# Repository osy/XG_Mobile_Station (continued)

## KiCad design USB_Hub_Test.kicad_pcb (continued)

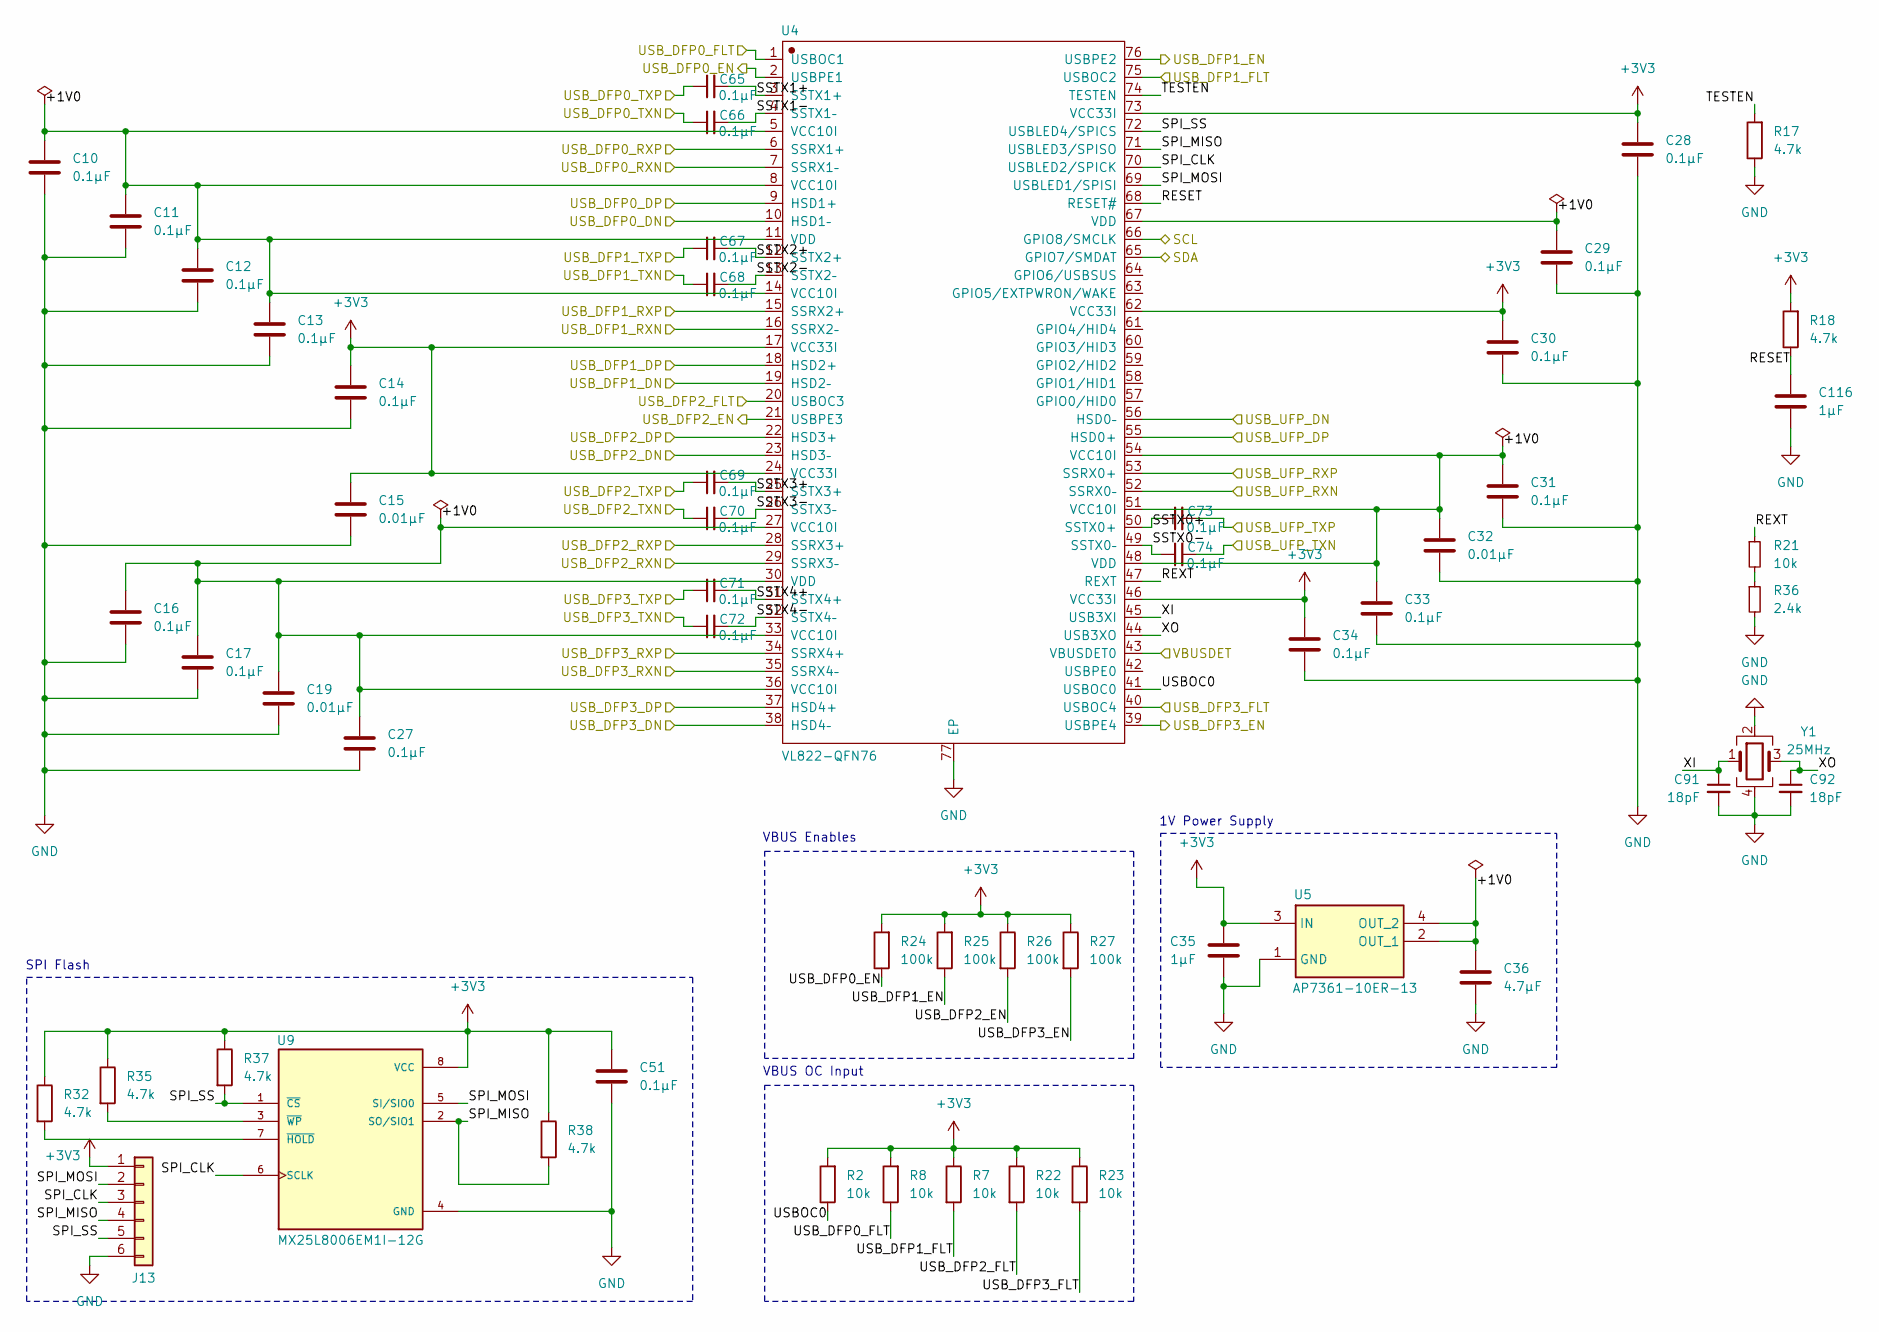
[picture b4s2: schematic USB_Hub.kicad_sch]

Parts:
C10, C11, C12, C13, C14, C16, C17, C27, C28, C29, C30, C31, C33, C34, C51, C65, C66, C67, C68, C69, C70, C71, C72, C73, C74: 0.1µF; C_0402_1005Metric; Part_Number CL05B104KB54PNC; LCSC C307331
C15, C19, C32: 0.01µF; C_0402_1005Metric; Part_Number CL05B103KB5NNNC; LCSC C15195
C35: 1µF; C_0603_1608Metric; Part_Number CL10A105KB8NNNC; LCSC C15849
C36: 4.7μF; C_0603_1608Metric; Part_Number CL10A475KO8NNNC; LCSC C19666
C91, C92: 18pF; C_0603_1608Metric; Part_Number CL10C180JB8NNNC; LCSC C1647
C116: 1µF; C_0402_1005Metric; Part_Number CL05A105KA5NQNC; LCSC C52923
J13: Conn_01x06; PinHeader_1x06_P2.54mm_Vertical; Part_Number 2.54-1*6; LCSC C5156615
R2, R7, R8, R21, R22, R23: 10k; R_0402_1005Metric; Part_Number 0402WGF1002TCE; LCSC C25744
R17, R18, R32, R35, R37, R38: 4.7k; R_0402_1005Metric; Part_Number 0402WGF4701TCE; LCSC C25900
R24, R25, R26, R27: 100k; R_0402_1005Metric; Part_Number 0402WGF1003TCE; LCSC C25741
R36: 2.4k; R_0402_1005Metric; Part_Number 0402WGF2401TCE; LCSC C25882
U4: VL822-QFN76; Part_Number VL822-QFN76; LCSC C2841047
U5: AP7361-10ER-13; SOT230P700X180-4N; Part_Number AP7361-10ER-13; LCSC C460389
U9: MX25L8006EM1I-12G; PARTREV 1.6; LCSC C106262
Y1: 25MHz; Crystal_SMD_3225-4Pin_3.2x2.5mm; Part_Number X322525MOB4SI; LCSC C9006

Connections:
+3V3: C14.1, C15.1, C28.1, C30.1, C34.1, C35.1, C51.1, J13.1, R2.2, R7.1, R8.2, R18.2, R22.1, R23.1, R24.2, R25.2, R26.1, R27.1, R32.1, R35.1, R37.1, R38.1, U4.17 (VCC33I), U4.24 (VCC33I), U4.46 (VCC33I), U4.62 (VCC33I), U4.73 (VCC33I), U5.3 (IN), U9.8 (VCC); also elsewhere on the board
/USB Hub/+1V0: C10.1, C11.1, C12.1, C13.1, C16.1, C17.1, C19.1, C27.1, C29.1, C31.1, C32.1, C33.1, C36.1, U4.5 (VCC10I), U4.8 (VCC10I), U4.11 (VDD), U4.14 (VCC10I), U4.27 (VCC10I), U4.30 (VDD), U4.33 (VCC10I), U4.36 (VCC10I), U4.48 (VDD), U4.51 (VCC10I), U4.54 (VCC10I), U4.67 (VDD), U5.2 (OUT_1), U5.4 (OUT_2)
/USB Hub/CS: J13.5, R37.2, U4.72 (USBLED4/SPICS), U9.1 (~CS); also elsewhere on the board
/USB Hub/MISO: J13.4, R38.2, U4.71 (USBLED3/SPISO), U9.2 (SO/SIO1); also elsewhere on the board
/USB Hub/MOSI: J13.2, U4.69 (USBLED1/SPISI), U9.5 (SI/SIO0); also elsewhere on the board
/USB Hub/RESET: C116.1, R18.1, U4.68 (RESET#)
/USB Hub/REXT: R21.1, U4.47 (REXT)
/USB Hub/SCL: U4.66 (GPIO8/SMCLK); also elsewhere on the board
/USB Hub/SCLK: J13.3, U4.70 (USBLED2/SPICK), U9.6 (SCLK); also elsewhere on the board
/USB Hub/SDA: U4.65 (GPIO7/SMDAT); also elsewhere on the board
/USB Hub/SSTX0+: C73.1, U4.50 (SSTX0+)
/USB Hub/SSTX0-: C74.1, U4.49 (SSTX0–)
/USB Hub/SSTX1+: C65.2, U4.3 (SSTX1+)
/USB Hub/SSTX1-: C66.2, U4.4 (SSTX1–)
/USB Hub/SSTX2+: C67.2, U4.12 (SSTX2+)
/USB Hub/SSTX2-: C68.2, U4.13 (SSTX2–)
/USB Hub/SSTX3+: C69.2, U4.25 (SSTX3+)
/USB Hub/SSTX3-: C70.2, U4.26 (SSTX3–)
/USB Hub/SSTX4+: C71.2, U4.31 (SSTX4+)
/USB Hub/SSTX4-: C72.2, U4.32 (SSTX4–)
/USB Hub/TESTEN: R17.2, U4.74 (TESTEN)
/USB Hub/USBOC0: R2.1, U4.41 (USBOC0)
/USB Hub/USB_DFP0_EN: R24.1, U4.2 (USBPE1)
/USB Hub/USB_DFP0_FLT: R8.1, U4.1 (USBOC1)
/USB Hub/USB_DFP1_EN: R25.1, U4.76 (USBPE2)
/USB Hub/USB_DFP1_FLT: R7.2, U4.75 (USBOC2)
/USB Hub/USB_DFP2_EN: R26.2, U4.21 (USBPE3)
/USB Hub/USB_DFP2_FLT: R22.2, U4.20 (USBOC3)
/USB Hub/USB_DFP3_EN: R27.2, U4.39 (USBPE4)
/USB Hub/USB_DFP3_FLT: R23.2, U4.40 (USBOC4)
/USB Hub/USB_UFP_DN: U4.56 (HSD0–); also elsewhere on the board
/USB Hub/USB_UFP_DP: U4.55 (HSD0+); also elsewhere on the board
/USB Hub/USB_UFP_RXN: U4.52 (SSRX0–); also elsewhere on the board
/USB Hub/USB_UFP_RXP: U4.53 (SSRX0+); also elsewhere on the board
/USB Hub/USB_UFP_TXN: C74.2; also elsewhere on the board
/USB Hub/USB_UFP_TXP: C73.2; also elsewhere on the board
/USB Hub/VBUSDET: U4.43 (VBUSDET0); also elsewhere on the board
/USB Hub/XI: C91.1, U4.45 (USB3XI), Y1.1
/USB Hub/XO: C92.1, U4.44 (USB3XO), Y1.3
/USB_DFP0_D1N: U4.10 (HSD1–); also elsewhere on the board
/USB_DFP0_D1P: U4.9 (HSD1+); also elsewhere on the board
/USB_DFP0_D2N: U4.19 (HSD2–); also elsewhere on the board
/USB_DFP0_D2P: U4.18 (HSD2+); also elsewhere on the board
/USB_DFP0_RX1N: U4.7 (SSRX1–); also elsewhere on the board
/USB_DFP0_RX1P: U4.6 (SSRX1+); also elsewhere on the board
/USB_DFP0_RX2N: U4.15 (SSRX2+); also elsewhere on the board
/USB_DFP0_RX2P: U4.16 (SSRX2–); also elsewhere on the board
/USB_DFP0_TX1N: C66.1; also elsewhere on the board
/USB_DFP0_TX1P: C65.1; also elsewhere on the board
/USB_DFP0_TX2N: C67.1; also elsewhere on the board
/USB_DFP0_TX2P: C68.1; also elsewhere on the board
/USB_DFP1_D1N: U4.23 (HSD3–); also elsewhere on the board
/USB_DFP1_D1P: U4.22 (HSD3+); also elsewhere on the board
/USB_DFP1_D2N: U4.38 (HSD4–); also elsewhere on the board
/USB_DFP1_D2P: U4.37 (HSD4+); also elsewhere on the board
/USB_DFP1_RX1N: U4.29 (SSRX3–); also elsewhere on the board
/USB_DFP1_RX1P: U4.28 (SSRX3+); also elsewhere on the board
/USB_DFP1_RX2N: U4.34 (SSRX4+); also elsewhere on the board
/USB_DFP1_RX2P: U4.35 (SSRX4–); also elsewhere on the board
/USB_DFP1_TX1N: C70.1; also elsewhere on the board
/USB_DFP1_TX1P: C69.1; also elsewhere on the board
/USB_DFP1_TX2N: C71.1; also elsewhere on the board
/USB_DFP1_TX2P: C72.1; also elsewhere on the board
GND: C10.2, C11.2, C12.2, C13.2, C14.2, C15.2, C16.2, C17.2, C19.2, C27.2, C28.2, C29.2, C30.2, C31.2, C32.2, C33.2, C34.2, C35.2, C36.2, C51.2, C91.2, C92.2, C116.2, J13.6, R17.1, R36.2, U4.77 (EP), U5.1 (GND), U9.4 (GND), Y1.2, Y1.4; also elsewhere on the board
unnamed: R21.2, R36.1
unnamed: R32.2, U9.7 (~HOLD)
unnamed: R35.2, U9.3 (~WP)

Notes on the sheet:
VBUS Enables
1V Power Supply
VBUS OC Input
SPI Flash

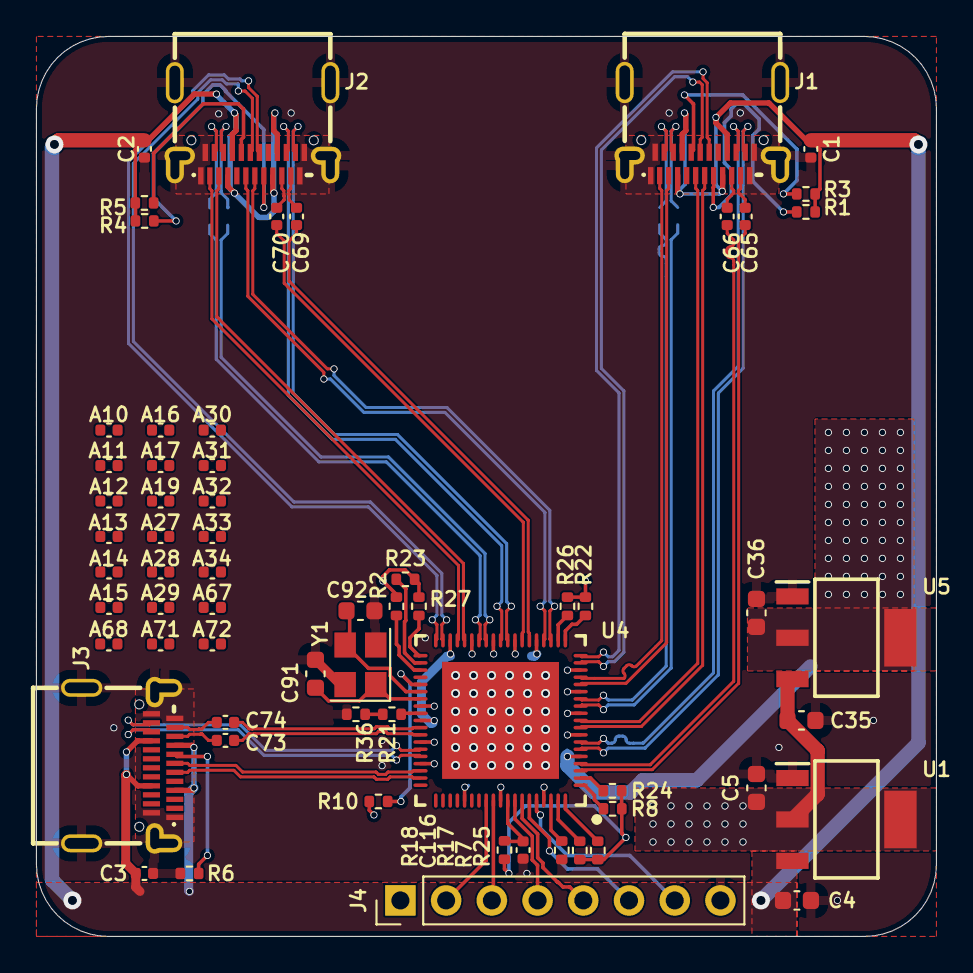
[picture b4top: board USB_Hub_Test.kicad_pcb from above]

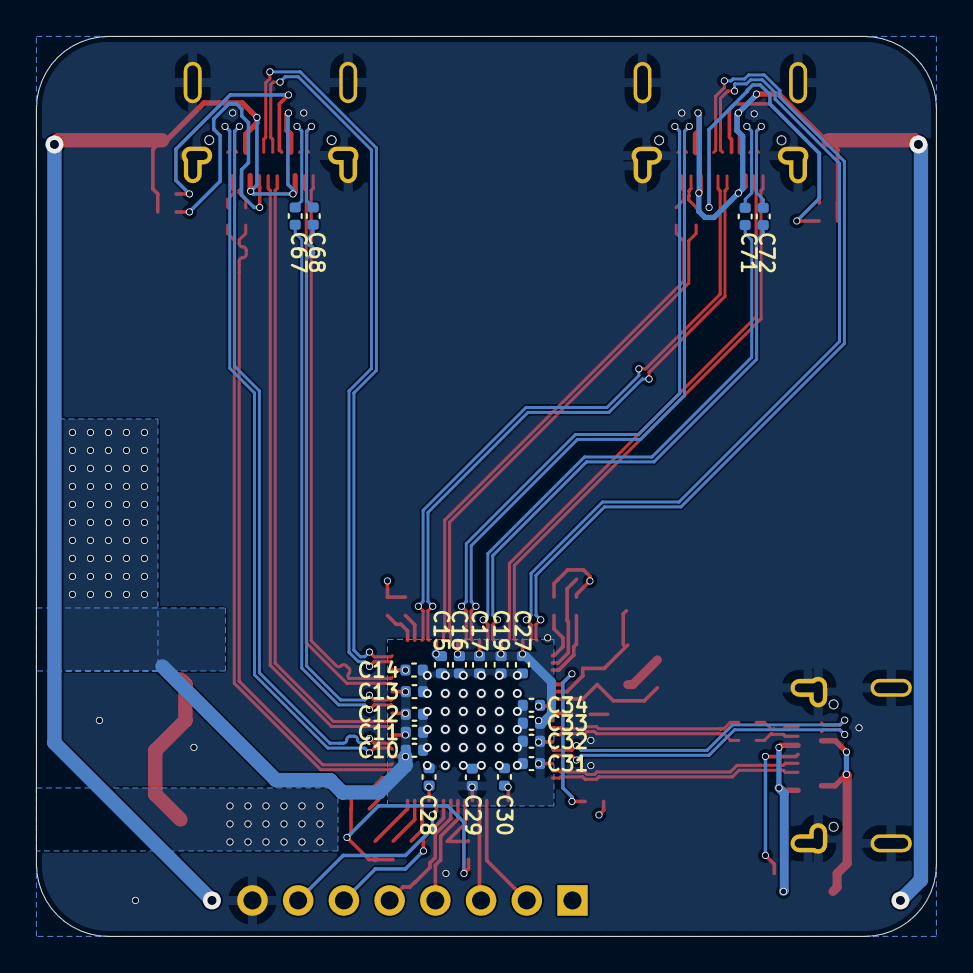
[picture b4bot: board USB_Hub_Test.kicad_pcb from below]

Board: 4 copper layers, 50.0 x 50.0 mm, 85 parts (21 on the bottom side), 71 nets.

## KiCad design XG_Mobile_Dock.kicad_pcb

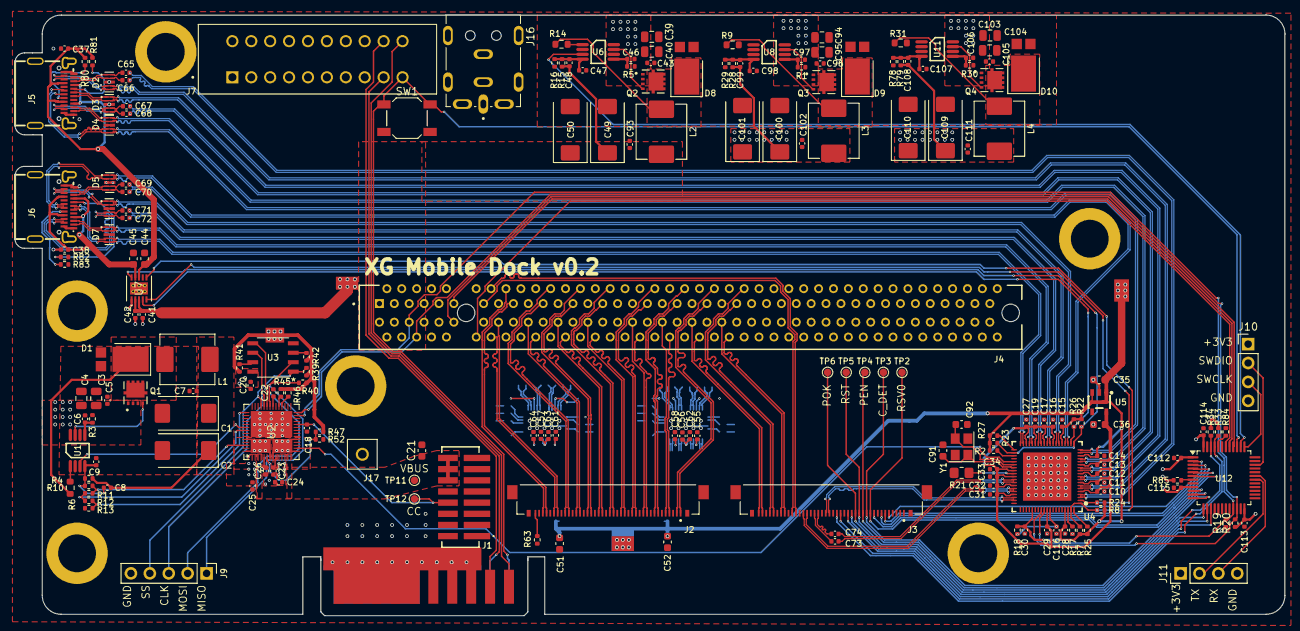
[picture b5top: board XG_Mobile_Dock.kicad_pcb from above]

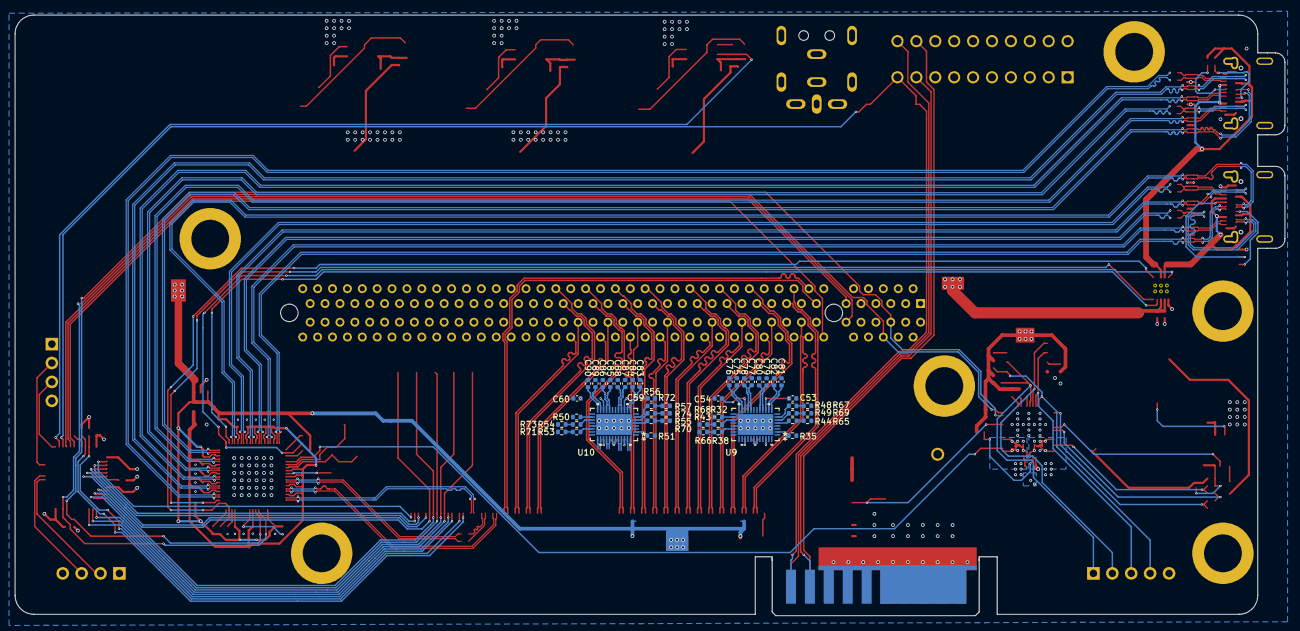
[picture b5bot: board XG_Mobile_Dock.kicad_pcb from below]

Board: 4 copper layers, 170.6 x 80.7 mm, 242 parts (46 on the bottom side), 215 nets.

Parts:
C1, C2, C49, C50, C100, C101, C109, C110: 47µF; CP_EIA-7343-43_Kemet-X
C3, C4, C39, C40, C94, C95, C103, C104: 22µF; C_0805_2012Metric
C5, C7, C10, C11, C12, C13, C14, C16, C17, C20, C27, C28, C29, C30, C31, C33, C34, C43, C65, C66, C67, C68, C69, C70, C71, C72, C73, C74, C93, C96, C102, C105, C111, C112, C113, C114: 0.1µF; C_0402_1005Metric
C6, C9, C46, C47, C97, C98, C106, C107: 1000pF; C_0402_1005Metric
C8, C48, C99, C108: 100pF; C_0402_1005Metric
C15, C19, C32: 0.01µF; C_0402_1005Metric
C18: 220pF; C_0402_1005Metric
C21, C35, C51, C52: 1µF; C_0603_1608Metric
C22, C23, C24, C25, C26, C115: 10µF; C_0402_1005Metric
C36: 4.7μF; C_0603_1608Metric
C37, C38, C41, C42, C53, C54, C55, C56, C57, C58, C59, C60, C61, C62, C63, C64: 0.1μF; C_0402_1005Metric
C44, C45: 22μF; C_0603_1608Metric
C75, C76, C77, C78, C79, C80, C81, C82, C83, C84, C85, C86, C87, C88, C89, C90: 220nF; C_0402_1005Metric
C91, C92: 22pF; C_0603_1608Metric
C116: 1µF; C_0402_1005Metric
D1, D8, D9, D10: PDS1040L-13; D_PowerDI-5
D2, D3, D4, D5, D6, D7: H5VU25U; AZ1045-04F
J1: 5-1775443-8
J2, J3: 20455-040E-76
J4: 3-2362375-4; SAMTEC_PCIE-164-02-F-D-TH-TR
J5, J6: USB_C_Receptacle; USB-C-SMD_TYPE-C-24P-QT
J7: Conn_02x10_Odd_Even; 5-5530843-0
J8: Conn_02x10_Odd_Even; 20P_Slot_Power
J9: Conn_01x05; PinHeader_1x05_P2.54mm_Vertical
J10: SWD; PinHeader_1x04_P2.54mm_Vertical
J11: UART; PinHeader_1x04_P2.54mm_Vertical
J16: 19V 5A DC; CUI_PJ-096H
J17: 8730; KEYSTONE_8730
L1, L2, L3, L4: 10µH; L_Abracon_ASPI-0630LR
Q1, Q2, Q3, Q4: AON7403; TRANS_AON7403
R1, R3, R30, R38, R43, R44, R48, R49, R53, R54, R55, R56, R57: 47k; R_0402_1005Metric
R2, R7, R8, R22, R23, R33, R34, R47, R63, R85: 10k; R_0402_1005Metric
R4: 49.9k; R_0402_1005Metric
R5: 68k; R_0402_1005Metric
R6, R9, R14, R31: 270; R_0603_1608Metric
R10, R12: 3.3k; R_0402_1005Metric
R11: 1.2k; R_0402_1005Metric
R13: 8.2k; R_0402_1005Metric
R15: 33k; R_0402_1005Metric
R16, R29: 3.9k; R_0402_1005Metric
R17, R18, R19, R20, R32, R39, R40, R41, R42, R45, R46, R50: 4.7k; R_0402_1005Metric
R21: 12.4k; R_0805_2012Metric_Pad1.20x1.40mm_HandSolder
R24, R25, R26, R27, R52: 100k; R_0402_1005Metric
R28, R65, R66, R67, R68, R69, R70, R71, R72, R73, R74, R79: 12k; R_0402_1005Metric
R35, R51, R84: 1k; R_0402_1005Metric
R78: 20k; R_0402_1005Metric
R80, R81, R82, R83: 22k; R_0402_1005Metric
SW1: SW_Push; SW_SPST_SKQG_WithStem
TP2, TP3, TP4, TP5, TP6, TP11, TP12: TestPoint_Small; TestPoint_Pad_D1.0mm
U1, U6, U8, U11: LM3489QMM/NOPB; LM3489QMM-NOPB
U2: TPS65987DDHRSHR
U3: MX25L8006EM1I-12G
U4: VL822-QFN76
U5: AP7331-10WG-7
U7: TPS2003CDRCR; DRC10_1P65X2P40_TEX
U9, U10: SN75LVPE4410RNQR
U12: STM32F030C8Tx; LQFP-48_7x7mm_P0.5mm
Y1: 25MHz; Crystal_SMD_3225-4Pin_3.2x2.5mm

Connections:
+3V3: C14.1, C15.1, C20.1, C26.1, C28.1, C30.1, C35.1, C51.1, C52.1, C55.1, C56.1, C57.1, C58.1, C61.1, C62.1, C63.1, C64.1, C108.1, C109.1, C110.1, C111.1, C112.1, C113.1, C114.1, C115.1, J3.1 (+3.3V), J3.2 (+3.3V), J3.3 (+3.3V), J3.4 (+3.3V), J4.A9, J4.A10, J4.B8, J4.B10, J10.1, J11.1, L4.2, R2.2, R7.1, R8.2, R18.2, R19.1, R20.1, R22.1, R23.1, R24.2, R25.2, R26.1, R27.1, R32.1, R33.1, R34.1, R39.1, R40.1, R41.1, R42.1, R45.2, R46.2, R47.1, R50.1, R78.1, R85.2, U2.5 (VIN_3V3), U3.8 (VCC), U4.17 (VCC33I), U4.24 (VCC33I), U4.62 (VCC33I), U4.73 (VCC33I), U5.1 (IN), U5.3 (EN), U9.31 (VDD), U9.34 (VDD), U9.35 (VDD), U9.38 (VDD), U10.31 (VDD), U10.34 (VDD), U10.35 (VDD), U10.38 (VDD), U12.1 (VDD), U12.9 (VDDA), U12.24 (VDD), U12.48 (VDD)
+5V: C41.1, C42.1, C99.1, C100.1, C101.1, C102.1, L3.2, R28.1, U7.2 (IN), U7.3 (IN)
+12V: C48.1, C49.1, C50.1, C93.1, J4.A2, J4.A3, J4.B1, J4.B2, J4.B3, L2.2, R15.1
+20V: C3.1, C4.1, C5.1, C6.1, C39.1, C40.1, C43.1, C46.1, C94.1, C95.1, C96.1, C97.1, C103.1, C104.1, C105.1, C106.1, J7.2, J7.4, J7.6, J7.8, J7.10, J7.12, J7.14, J7.16, J8.2, J8.4, J8.6, J8.8, J8.10, J8.12, J8.14, J8.16, J16.3, J16.4, Q1.1, Q2.1, Q3.1, Q4.1, R1.1, R3.1, R5.1, R30.1, U1.8 (VIN), U6.8 (VIN), U8.8 (VIN), U11.8 (VIN)
/12V_EN: U6.3 (EN), U12.38 (PA15)
/AC_LOSS: J3.15 (P_AC_LOSS), U12.14 (PA4)
/CLKN: J3.30 (PCIE_CLKN), J4.A14
/CLKP: J3.31 (PCIE_CLKP), J4.A13
/CLKREQ#: J4.B12, U12.42 (PB6)
/CON_DET: J3.11 (CON_DET), TP3.1, U12.10 (PA0)
/C_DN: J3.21 (USB_DM), U4.56 (HSD0–)
/C_DP: J3.22 (USB_DP), U4.55 (HSD0+)
/C_RXN: J3.27 (USB_TXN), U4.52 (SSRX0–)
/C_RXP: J3.28 (USB_TXP), U4.53 (SSRX0+)
/C_TXN: C74.2, J3.24 (USB_RXN)
/C_TXP: C73.2, J3.25 (USB_RXP)
/DET: J2.40 (CON_DET_TOWER#), R63.1
/LED_RED#: J3.7 (LED_R), U12.4 (PC15)
/LED_WHITE#: J3.6 (LED_W), U12.3 (PC14)
/LOCK_DET: J3.9 (CON_SW1_DET), U12.5 (PF0)
/LOCK_SW: J3.5 (LOCK_SW), U12.2 (PC13)
/MCU/RX: J11.3, U12.31 (PA10)
/MCU/SWCLK: J10.3, U12.37 (PA14)
/MCU/SWDIO: J10.2, U12.34 (PA13)
/MCU/TX: J11.2, U12.30 (PA9)
/MCU_IRQ#: J3.16 (MCU_IRQ#), U12.15 (PA5)
/PCIe Redriver/EN_SMB_0: R35.2, U9.2 (EN_SMB)
/PCIe Redriver/EN_SMB_1: R51.2, U10.2 (EN_SMB)
/PCIe Redriver/EQ0_ADDR0_0: R48.1, U9.7 (EQ0_ADDR0)
/PCIe Redriver/EQ0_ADDR0_1: R56.1, U10.7 (EQ0_ADDR0)
/PCIe Redriver/EQ1_ADDR1_0: R49.1, U9.6 (EQ1_ADDR1)
/PCIe Redriver/EQ1_ADDR1_1: R57.1, U10.6 (EQ1_ADDR1)
/PCIe Redriver/GAIN_0: R44.1, U9.5 (GAIN)
/PCIe Redriver/GAIN_1: R55.1, U10.5 (GAIN)
/PCIe Redriver/RX_DET_0: R38.1, U9.26 (RX_DET)
/PCIe Redriver/RX_DET_1: R53.1, U10.26 (RX_DET)
/PCIe Redriver/SCL: U9.3 (SCL), U10.3 (SCL)
/PCIe Redriver/SDA: U9.4 (SDA), U10.4 (SDA)
/PCIe Redriver/TX0CN: C89.2, U10.19 (TX0N)
/PCIe Redriver/TX0CP: C90.2, U10.20 (TX0P)
/PCIe Redriver/TX1CN: C85.2, U10.16 (TX1N)
/PCIe Redriver/TX1CP: C86.2, U10.17 (TX1P)
/PCIe Redriver/TX2CN: C87.2, U10.12 (TX2N)
/PCIe Redriver/TX2CP: C88.2, U10.13 (TX2P)
/PCIe Redriver/TX3CN: C83.2, U10.9 (TX3N)
/PCIe Redriver/TX3CP: C84.2, U10.10 (TX3P)
/PCIe Redriver/TX4CN: C75.2, U9.19 (TX0N)
/PCIe Redriver/TX4CP: C76.2, U9.20 (TX0P)
/PCIe Redriver/TX5CN: C77.2, U9.16 (TX1N)
/PCIe Redriver/TX5CP: C78.2, U9.17 (TX1P)
/PCIe Redriver/TX6CN: C79.2, U9.12 (TX2N)
/PCIe Redriver/TX6CP: C80.2, U9.13 (TX2P)
/PCIe Redriver/TX7CN: C81.2, U9.9 (TX3N)
/PCIe Redriver/TX7CP: C82.2, U9.10 (TX3P)
/PCIe Redriver/VOD_0: R43.1, U9.23 (VOD)
/PCIe Redriver/VOD_1: R54.1, U10.23 (VOD)
/PERST#: J4.A11, U12.41 (PB5)
/PWREN#: J3.12 (PWR_EN#), TP4.1, U12.11 (PA1)
/PWROK: J3.14 (PWROK), TP6.1, U12.13 (PA3)
/PWR_SW: J7.19, J8.19, SW1.1, U12.39 (PB3)
/RST#: J3.13 (RST#), TP5.1, U12.12 (PA2)
/RSV0: J3.10, TP2.1, U12.6 (PF1)
/RX0N: J2.37 (PCIE_TXN0), J4.A17
/RX0P: J2.38 (PCIE_TXP0), J4.A16
/RX1N: J2.31 (PCIE_TXN1), J4.A21
/RX1P: J2.32 (PCIE_TXP1), J4.A22
/RX2N: J2.25 (PCIE_TXN2), J4.A25
/RX2P: J2.26 (PCIE_TXP2), J4.A26
/RX3N: J2.19 (PCIE_TXN3), J4.A29
/RX3P: J2.20 (PCIE_TXP3), J4.A30
/RX4N: J2.13 (PCIE_TXN4), J4.A35
/RX4P: J2.14 (PCIE_TXP4), J4.A36
/RX5N: J2.7 (PCIE_TXN5), J4.A39
/RX5P: J2.8 (PCIE_TXP5), J4.A40
/RX6N: J2.1 (PCIE_TXN6), J4.A43
/RX6P: J2.2 (PCIE_TXP6), J4.A44
/RX7N: J3.36 (PCIE_TXN7), J4.A47
/RX7P: J3.37 (PCIE_TXP7), J4.A48
/SCL1: J3.19 (SMB1_CLK), R33.2, U12.45 (PB8)
/SCL2: J4.B5, R19.2, U2.27 (I2C1_SCL), U4.66 (GPIO8/SMCLK), U12.21 (PB10)
/SDA1: J3.18 (SMB1_DAT), R34.2, U12.46 (PB9)
/SDA2: J4.B6, R20.2, U2.28 (I2C1_SDA), U4.65 (GPIO7/SMDAT), U12.22 (PB11)
/TX0N: J2.34 (PCIE_RXN0), J4.B15
/TX0P: J2.35 (PCIE_RXP0), J4.B14
/TX1N: J2.28 (PCIE_RXN1), J4.B20
/TX1P: J2.29 (PCIE_RXP1), J4.B19
/TX2N: J2.22 (PCIE_RXN2), J4.B24
/TX2P: J2.23 (PCIE_RXP2), J4.B23
/TX3N: J2.16 (PCIE_RXN3), J4.B28
/TX3P: J2.17 (PCIE_RXP3), J4.B27
/TX4N: J2.10 (PCIE_RXN4), J4.B34
/TX4P: J2.11 (PCIE_RXP4), J4.B33
/TX5N: J2.4 (PCIE_RXN5), J4.B38
/TX5P: J2.5 (PCIE_RXP5), J4.B37
/TX6N: J3.39 (PCIE_RXN6), J4.B42
/TX6P: J3.40 (PCIE_RXP6), J4.B41
/TX7N: J3.33 (PCIE_RXN7), J4.B46
/TX7P: J3.34 (PCIE_RXP7), J4.B45
/USB C DFPs/USB_DFP0_D1N: D3.2 (I/O_2), D3.9 (NC), J5.A7 (D-), U4.10 (HSD1–)
/USB C DFPs/USB_DFP0_D1P: D3.1 (I/O_1), D3.10 (NC), J5.A6 (D+), U4.9 (HSD1+)
/USB C DFPs/USB_DFP0_D2N: D4.5 (I/O_4), D4.6 (NC), J5.B7 (D-), U4.19 (HSD2–)
/USB C DFPs/USB_DFP0_D2P: D4.4 (I/O_3), D4.7 (NC), J5.B6 (D+), U4.18 (HSD2+)
/USB C DFPs/USB_DFP0_RX1N: D2.5 (I/O_4), D2.6 (NC), J5.B10 (RX1-), U4.7 (SSRX1–)
/USB C DFPs/USB_DFP0_RX1P: D2.4 (I/O_3), D2.7 (NC), J5.B11 (RX1+), U4.6 (SSRX1+)
/USB C DFPs/USB_DFP0_RX2N: D4.1 (I/O_1), D4.10 (NC), J5.A10 (RX2-), U4.15 (SSRX2+)
/USB C DFPs/USB_DFP0_RX2P: D4.2 (I/O_2), D4.9 (NC), J5.A11 (RX2+), U4.16 (SSRX2–)
/USB C DFPs/USB_DFP0_TX1N: C66.1, D2.2 (I/O_2), D2.9 (NC), J5.A3 (TX1-)
/USB C DFPs/USB_DFP0_TX1P: C65.1, D2.1 (I/O_1), D2.10 (NC), J5.A2 (TX1+)
/USB C DFPs/USB_DFP0_TX2N: C67.1, D3.4 (I/O_3), D3.7 (NC), J5.B3 (TX2-)
/USB C DFPs/USB_DFP0_TX2P: C68.1, D3.5 (I/O_4), D3.6 (NC), J5.B2 (TX2+)
/USB C DFPs/USB_DFP0_VBUS: C37.1, C44.1, J5.A4 (VBUS), J5.A9 (VBUS), J5.B4 (VBUS), J5.B9 (VBUS), R80.2, R81.1, U7.8 (OUT2)
/USB C DFPs/USB_DFP1_D1N: D7.5 (I/O_4), D7.6 (NC), J6.A7 (D-), U4.38 (HSD4–)
/USB C DFPs/USB_DFP1_D1P: D7.4 (I/O_3), D7.7 (NC), J6.A6 (D+), U4.37 (HSD4+)
/USB C DFPs/USB_DFP1_D2N: D5.2 (I/O_2), D5.9 (NC), J6.B7 (D-), U4.23 (HSD3–)
/USB C DFPs/USB_DFP1_D2P: D5.1 (I/O_1), D5.10 (NC), J6.B6 (D+), U4.22 (HSD3+)
/USB C DFPs/USB_DFP1_RX1N: D6.2 (I/O_2), D6.9 (NC), J6.B10 (RX1-), U4.29 (SSRX3–)
/USB C DFPs/USB_DFP1_RX1P: D6.1 (I/O_1), D6.10 (NC), J6.B11 (RX1+), U4.28 (SSRX3+)
/USB C DFPs/USB_DFP1_RX2N: D7.1 (I/O_1), D7.10 (NC), J6.A10 (RX2-), U4.34 (SSRX4+)
/USB C DFPs/USB_DFP1_RX2P: D7.2 (I/O_2), D7.9 (NC), J6.A11 (RX2+), U4.35 (SSRX4–)
/USB C DFPs/USB_DFP1_TX1N: C70.1, D5.5 (I/O_4), D5.6 (NC), J6.A3 (TX1-)
/USB C DFPs/USB_DFP1_TX1P: C69.1, D5.4 (I/O_3), D5.7 (NC), J6.A2 (TX1+)
/USB C DFPs/USB_DFP1_TX2N: C71.1, D6.4 (I/O_3), D6.7 (NC), J6.B3 (TX2-)
/USB C DFPs/USB_DFP1_TX2P: C72.1, D6.5 (I/O_4), D6.6 (NC), J6.B2 (TX2+)
/USB C DFPs/USB_DFP1_VBUS: C38.1, C45.1, J6.A4 (VBUS), J6.A9 (VBUS), J6.B4 (VBUS), J6.B9 (VBUS), R82.2, R83.1, U7.9 (OUT1)
/USB Hub/+1V0: C10.1, C11.1, C12.1, C13.1, C16.1, C17.1, C19.1, C27.1, C29.1, C31.1, C32.1, C33.1, C34.1, C36.1, U4.5 (VCC10I), U4.8 (VCC10I), U4.11 (VDD), U4.14 (VCC10I), U4.27 (VCC10I), U4.30 (VDD), U4.33 (VCC10I), U4.36 (VCC10I), U4.46 (VCC33I), U4.48 (VDD), U4.51 (VCC10I), U4.54 (VCC10I), U4.67 (VDD), U5.5 (OUT)
/USB Hub/RESET: C116.1, R18.1, U4.68 (RESET#)
/USB Hub/REXT: R21.1, U4.47 (REXT)
/USB Hub/SSTX0+: C73.1, U4.50 (SSTX0+)
/USB Hub/SSTX0-: C74.1, U4.49 (SSTX0–)
/USB Hub/SSTX1+: C65.2, U4.3 (SSTX1+)
/USB Hub/SSTX1-: C66.2, U4.4 (SSTX1–)
/USB Hub/SSTX2+: C67.2, U4.12 (SSTX2+)
/USB Hub/SSTX2-: C68.2, U4.13 (SSTX2–)
/USB Hub/SSTX3+: C69.2, U4.25 (SSTX3+)
/USB Hub/SSTX3-: C70.2, U4.26 (SSTX3–)
/USB Hub/SSTX4+: C71.2, U4.31 (SSTX4+)
/USB Hub/SSTX4-: C72.2, U4.32 (SSTX4–)
/USB Hub/TESTEN: R17.2, U4.74 (TESTEN)
/USB Hub/USBOC0: R2.1, U4.41 (USBOC0)
/USB Hub/USB_DFP0_EN: R24.1, U4.2 (USBPE1), U7.5 (EN2)
/USB Hub/USB_DFP0_FLT: R7.2, R8.1, U4.1 (USBOC1), U4.75 (USBOC2), U7.6 (*FLT2)
/USB Hub/USB_DFP1_EN: R25.1, U4.76 (USBPE2)
/USB Hub/USB_DFP2_EN: R26.2, U4.21 (USBPE3), U7.4 (EN1)
/USB Hub/USB_DFP2_FLT: R22.2, R23.2, U4.20 (USBOC3), U4.40 (USBOC4), U7.10 (*FLT1)
/USB Hub/USB_DFP3_EN: R27.2, U4.39 (USBPE4)
/USB Hub/VBUSDET: U2.16 (GPIO0), U4.43 (VBUSDET0)
/USB Hub/XI: C91.1, U4.45 (USB3XI), Y1.1
/USB Hub/XO: C92.1, U4.44 (USB3XO), Y1.3
/USB PD Charger/BOOT: R47.2, R52.1, U2.6 (ADCIN1)
/USB PD Charger/CC: C18.1, J1.13 (CC), TP12.1, U2.24 (C_CC1)
/USB PD Charger/DRAIN1: U2.8 (DRAIN1), U2.15 (DRAIN1), U2.19 (DRAIN1), U2.58 (DRAIN1)
/USB PD Charger/DRAIN2: U2.7 (DRAIN2), U2.52 (DRAIN2), U2.56 (DRAIN2), U2.57 (DRAIN2)
/USB PD Charger/LDO_3V3: C23.1, U2.9 (LDO_3V3)
/USB PD Charger/PDO_1: R12.2, R13.1, U2.43 (GPIO15)
/USB PD Charger/PDO_2: R11.2, R12.1, U2.49 (GPIO17)
/USB PD Charger/PDO_3: R10.2, R11.1, U2.54 (GPIO20)
/USB PD Charger/POWER_EN: U1.3 (EN), U2.48 (GPIO16)
/USB PD Charger/SPI_CLK: J9.3, U2.38 (SPI_CLK), U3.6 (SCLK)
/USB PD Charger/SPI_MISO: J9.1, R40.2, U2.36 (SPI_MISO), U3.2 (SO/SIO1)
/USB PD Charger/SPI_MOSI: J9.2, U2.37 (SPI_MOSI), U3.5 (SI/SIO0)
/USB PD Charger/SPI_SS: J9.4, R39.2, U2.39 (SPI_SS), U3.1 (~CS)
/USB PD Charger/VBUS: C21.1, J1.9 (VBUS), J1.10 (VBUS), J1.11 (VBUS), TP11.1, U2.3 (VBUS2), U2.4 (VBUS2), U2.13 (VBUS1), U2.14 (VBUS1)
/WAKE#: J4.B11, U12.40 (PB4)
GND: C1.2, C2.2, C3.2, C4.2, C5.2, C7.2, C9.2, C10.2, C11.2, C12.2, C13.2, C14.2, C15.2, C16.2, C17.2, C18.2, C19.2, C20.2, C21.2, C22.2, C23.2, C24.2, C25.2, C26.2, C27.2, C28.2, C29.2, C30.2, C31.2, C32.2, C33.2, C34.2, C35.2, C36.2, C37.2, C38.2, C39.2, C40.2, C41.2, C42.2, C43.2, C44.2, C45.2, C47.2, C49.2, C50.2, C51.2, C52.2, C53.2, C54.2, C55.2, C56.2, C57.2, C58.2, C59.2, C60.2, C61.2, C62.2, C63.2, C64.2, C91.2, C92.2, C93.2, C94.2, C95.2, C96.2, C98.2, C100.2, C101.2, C102.2, C103.2, C104.2, C105.2, C107.2, C109.2, C110.2, C111.2, C112.2, C113.2, C114.2, C115.2, C116.2, D1.2 (A), D2.3 (GND), D2.8 (GND), D3.3 (GND), D3.8 (GND), D4.3 (GND), D4.8 (GND), D5.3 (GND), D5.8 (GND), D6.3 (GND), D6.8 (GND), D7.3 (GND), D7.8 (GND), D8.2 (A), D9.2 (A), D10.2 (A), J1.14 (GND), J1.15 (GND), J1.16 (GND), J2.3 (GND), J2.6 (GND), J2.9 (GND), J2.12 (GND), J2.15 (GND), J2.18 (GND), J2.21 (GND), J2.24 (GND), J2.27 (GND), J2.30 (GND), J2.33 (GND), J2.36 (GND), J2.39 (GND), J2.S1 (SHIELD), J2.S2 (SHIELD), J2.S3 (SHIELD), J2.S4 (SHIELD), J3.17 (GND), J3.20 (GND), J3.23 (GND), J3.26 (GND), J3.29 (GND), J3.32 (GND), J3.35 (GND), J3.38 (GND), J3.S1 (SHIELD), J3.S2 (SHIELD), J3.S3 (SHIELD), J3.S4 (SHIELD), J4.A4, J4.A12, J4.A15, J4.A18, J4.A20, J4.A23, J4.A24, J4.A27, J4.A28, J4.A31, J4.A34, J4.A37, J4.A38, J4.A41, J4.A42, J4.A45, J4.A46, J4.A49, J4.A51, J4.A54, J4.A55, J4.A58, J4.A59, J4.A62, J4.A63, J4.A66, J4.A67, J4.A70, J4.A71, J4.A74, J4.A75, J4.A78, J4.A79, J4.A82, J4.B4, J4.B7, J4.B13, J4.B16, J4.B18, J4.B21, J4.B22, J4.B25, J4.B26, J4.B29, J4.B32, J4.B35, J4.B36, J4.B39, J4.B40, J4.B43, J4.B44, J4.B47, J4.B49, J4.B52, J4.B53, J4.B56, J4.B57, J4.B60, J4.B61, J4.B64, J4.B65, J4.B68, J4.B69, J4.B72, J4.B73, J4.B76, J4.B77, J4.B80, J5.A1 (GND), J5.A12 (GND), J5.B1 (GND), J5.B12 (GND), J5.S1 (SHIELD), J6.A1 (GND), J6.A12 (GND), J6.B1 (GND)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
unnamed: C53.1, U9.11 (VREG)
unnamed: C54.1, U9.18 (VREG)
unnamed: C59.1, U10.11 (VREG)
unnamed: C60.1, U10.18 (VREG)
unnamed: D1.1 (K), L1.1, Q1.5_8, R6.2
unnamed: D8.1 (K), L2.1, Q2.5_8, R14.2
unnamed: D9.1 (K), L3.1, Q3.5_8, R9.2
unnamed: D10.1 (K), L4.1, Q4.5_8, R31.2
unnamed: J5.A5 (CC1), R80.1
unnamed: J5.B5 (CC2), R81.2
unnamed: J6.A5 (CC1), R82.1
unnamed: J6.B5 (CC2), R83.2
unnamed: J7.17, J8.17
unnamed: J7.18, J8.18
unnamed: J7.20, J8.20
unnamed: R38.2, R66.1
unnamed: R43.2, R68.1
unnamed: R44.2, R65.1
unnamed: R48.2, R67.1
unnamed: R49.2, R69.1
unnamed: R53.2, R71.1
unnamed: R54.2, R73.1
unnamed: R55.2, R70.1
unnamed: R56.2, R72.1
unnamed: R57.2, R74.1
unnamed: C6.2, R3.2, U1.5 (ADJ)
unnamed: C8.2, C9.1, R4.2, R10.1, U1.4 (FB)
unnamed: R6.1, U1.1 (ISENSE)
unnamed: Q1.4, U1.7 (PGATE)
unnamed: R46.1, U2.32 (I2C2_SCL)
unnamed: R45.1, U2.33 (I2C2_SDA)
unnamed: C22.1, U2.35 (LDO_1V8)
unnamed: R41.2, U3.7 (~HOLD)
unnamed: R42.2, U3.3 (~WP)
unnamed: C46.2, R5.2, U6.5 (ADJ)
unnamed: C47.1, C48.2, R15.2, R16.2, U6.4 (FB)
unnamed: R14.1, U6.1 (ISENSE)
unnamed: Q2.4, U6.7 (PGATE)
unnamed: C97.2, R1.2, U8.5 (ADJ)
unnamed: C98.1, C99.2, R28.2, R29.2, U8.4 (FB)
unnamed: R9.1, U8.1 (ISENSE)
unnamed: Q3.4, U8.7 (PGATE)
unnamed: R32.2, U9.22 (RSVD2)
unnamed: R50.2, U10.22 (RSVD2)
unnamed: C106.2, R30.2, U11.5 (ADJ)
unnamed: C107.1, C108.2, R78.2, R79.1, U11.4 (FB)
unnamed: R31.1, U11.1 (ISENSE)
unnamed: Q4.4, U11.7 (PGATE)
unnamed: R84.2, U12.44 (BOOT0)
unnamed: R85.1, U12.7 (NRST)
PP_HV: C1.1, C2.1, C7.1, C8.1, C24.1, C25.1, L1.2, R4.1, U2.1 (PP_HV2), U2.2 (PP_HV2), U2.11 (PP_HV1), U2.12 (PP_HV1)

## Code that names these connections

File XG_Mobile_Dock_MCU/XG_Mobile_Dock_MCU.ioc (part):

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Mcu.Name=STM32F030C8Tx
Mcu.Package=LQFP48
Mcu.UserName=STM32F030C8Tx
PA0.GPIOParameters=GPIO_PuPd,GPIO_Label,GPIO_ModeDefaultEXTI
PA0.GPIO_Label=CON_DET
PA0.GPIO_ModeDefaultEXTI=GPIO_MODE_IT_RISING_FALLING
PA0.GPIO_PuPd=GPIO_PULLUP
PA0.Signal=GPXTI0
PA1.GPIOParameters=GPIO_PuPd,GPIO_Label,GPIO_ModeDefaultEXTI
PA1.GPIO_Label=PWREN
PA1.GPIO_ModeDefaultEXTI=GPIO_MODE_IT_RISING_FALLING
PA1.GPIO_PuPd=GPIO_PULLUP
PA1.Signal=GPXTI1
PA10.Mode=Asynchronous
PA10.Signal=USART1_RX
PA12.GPIOParameters=PinState,GPIO_Label
PA12.GPIO_Label=FAN_ON
PA12.PinState=GPIO_PIN_RESET
PA12.Signal=GPIO_Output
PA13.Mode=Serial_Wire
PA13.Signal=SYS_SWDIO
PA14.Mode=Serial_Wire
PA14.Signal=SYS_SWCLK
PA15.GPIOParameters=PinState,GPIO_PuPd,GPIO_Label,GPIO_ModeDefaultOutputPP
PA15.GPIO_Label=PCI_12V_EN
PA15.GPIO_ModeDefaultOutputPP=GPIO_MODE_OUTPUT_OD
PA15.GPIO_PuPd=GPIO_NOPULL
PA15.PinState=GPIO_PIN_RESET
PA15.Signal=GPIO_Output
PA2.GPIOParameters=GPIO_PuPd,GPIO_Label,GPIO_ModeDefaultEXTI
PA2.GPIO_Label=RST
PA2.GPIO_ModeDefaultEXTI=GPIO_MODE_IT_RISING_FALLING
PA2.GPIO_PuPd=GPIO_PULLUP
PA2.Signal=GPXTI2
PA3.GPIOParameters=PinState,GPIO_PuPd,GPIO_Label,GPIO_ModeDefaultOutputPP
PA3.GPIO_Label=PWROK
PA3.GPIO_ModeDefaultOutputPP=GPIO_MODE_OUTPUT_PP
PA3.GPIO_PuPd=GPIO_NOPULL
PA3.PinState=GPIO_PIN_RESET
PA3.Signal=GPIO_Output
PA4.GPIOParameters=PinState,GPIO_PuPd,GPIO_Label,GPIO_ModeDefaultOutputPP
PA4.GPIO_Label=AC_LOSS
PA4.GPIO_ModeDefaultOutputPP=GPIO_MODE_OUTPUT_PP
PA4.GPIO_PuPd=GPIO_PULLDOWN
PA4.PinState=GPIO_PIN_RESET
PA4.Signal=GPIO_Output
PA5.GPIOParameters=PinState,GPIO_PuPd,GPIO_Label,GPIO_ModeDefaultOutputPP
PA5.GPIO_Label=MCU_IRQ
PA5.GPIO_ModeDefaultOutputPP=GPIO_MODE_OUTPUT_OD
PA5.GPIO_PuPd=GPIO_PULLUP
PA5.PinState=GPIO_PIN_SET
PA5.Signal=GPIO_Output
PA9.Mode=Asynchronous
PA9.Signal=USART1_TX
PB1.Mode=IN9
PB1.Signal=ADC_IN9
PB10.Mode=I2C
PB10.Signal=I2C2_SCL
PB11.Mode=I2C
PB11.Signal=I2C2_SDA
PB12.GPIOParameters=PinState,GPIO_PuPd,GPIO_Label,GPIO_ModeDefaultOutputPP
PB12.GPIO_Label=PWR_SW
PB12.GPIO_ModeDefaultOutputPP=GPIO_MODE_OUTPUT_OD
PB12.GPIO_PuPd=GPIO_NOPULL
PB12.PinState=GPIO_PIN_SET
PB12.Signal=GPIO_Output
PB13.GPIOParameters=GPIO_PuPd,GPIO_Label
PB13.GPIO_Label=SYS_ON
PB13.GPIO_PuPd=GPIO_PULLDOWN
PB13.Signal=GPIO_Input
PB14.GPIOParameters=GPIO_PuPd,GPIO_Label
PB14.GPIO_Label=SYS_DET
PB14.GPIO_PuPd=GPIO_PULLUP
PB14.Signal=GPIO_Input
PB2.GPIOParameters=PinState,GPIO_Label
PB2.GPIO_Label=HP_SHDN
PB2.PinState=GPIO_PIN_SET
PB2.Signal=GPIO_Output
PB3.GPIOParameters=GPIO_Speed,PinState,GPIO_Label
PB3.GPIO_Label=FAN_PWM
PB3.GPIO_Speed=GPIO_SPEED_FREQ_HIGH
PB3.PinState=GPIO_PIN_RESET
PB3.Signal=GPIO_Output
PB4.GPIOParameters=PinState,GPIO_PuPd,GPIO_Label,GPIO_ModeDefaultOutputPP
PB4.GPIO_Label=WAKE
PB4.GPIO_ModeDefaultOutputPP=GPIO_MODE_OUTPUT_OD
PB4.GPIO_PuPd=GPIO_PULLUP
PB4.PinState=GPIO_PIN_SET
PB4.Signal=GPIO_Output
PB5.GPIOParameters=PinState,GPIO_PuPd,GPIO_Label,GPIO_ModeDefaultOutputPP
PB5.GPIO_Label=PERST
PB5.GPIO_ModeDefaultOutputPP=GPIO_MODE_OUTPUT_OD
PB5.GPIO_PuPd=GPIO_PULLUP
PB5.PinState=GPIO_PIN_SET
PB5.Signal=GPIO_Output
PB6.GPIOParameters=PinState,GPIO_PuPd,GPIO_Label,GPIO_ModeDefaultOutputPP
PB6.GPIO_Label=CLKREQ
PB6.GPIO_ModeDefaultOutputPP=GPIO_MODE_OUTPUT_OD
PB6.GPIO_PuPd=GPIO_PULLUP
PB6.PinState=GPIO_PIN_SET
PB6.Signal=GPIO_Output
PB8.Mode=I2C
PB8.Signal=I2C1_SCL
PB9.Mode=I2C
PB9.Signal=I2C1_SDA
PC13.GPIOParameters=GPIO_PuPd,GPIO_Label,GPIO_ModeDefaultEXTI
PC13.GPIO_Label=LOCK_SW
PC13.GPIO_ModeDefaultEXTI=GPIO_MODE_IT_RISING_FALLING
PC13.GPIO_PuPd=GPIO_PULLUP
PC13.Signal=GPXTI13
PC14-OSC32_IN.GPIOParameters=PinState,GPIO_PuPd,GPIO_Label,GPIO_ModeDefaultOutputPP
PC14-OSC32_IN.GPIO_Label=LED_WHITE
PC14-OSC32_IN.GPIO_ModeDefaultOutputPP=GPIO_MODE_OUTPUT_OD
PC14-OSC32_IN.GPIO_PuPd=GPIO_NOPULL
PC14-OSC32_IN.PinState=GPIO_PIN_SET
PC14-OSC32_IN.Signal=GPIO_Output
PC15-OSC32_OUT.GPIOParameters=PinState,GPIO_PuPd,GPIO_Label,GPIO_ModeDefaultOutputPP
PC15-OSC32_OUT.GPIO_Label=LED_RED
PC15-OSC32_OUT.GPIO_ModeDefaultOutputPP=GPIO_MODE_OUTPUT_OD
PC15-OSC32_OUT.GPIO_PuPd=GPIO_NOPULL
PC15-OSC32_OUT.PinState=GPIO_PIN_SET
PC15-OSC32_OUT.Signal=GPIO_Output
PF0-OSC_IN.GPIOParameters=GPIO_Label
PF0-OSC_IN.GPIO_Label=LOCK_DET
PF0-OSC_IN.Signal=GPIO_Output
PF1-OSC_OUT.GPIOParameters=GPIO_Label
PF1-OSC_OUT.GPIO_Label=RSV0
PF1-OSC_OUT.Signal=GPIO_Input
PF7.GPIOParameters=PinState,GPIO_PuPd,GPIO_Label,GPIO_ModeDefaultOutputPP
PF7.GPIO_Label=CASE_LED
PF7.GPIO_ModeDefaultOutputPP=GPIO_MODE_OUTPUT_OD
PF7.GPIO_PuPd=GPIO_NOPULL
PF7.PinState=GPIO_PIN_SET
PF7.Signal=GPIO_Output
RCC.SYSCLKFreq_VALUE=32000000
RCC.SYSCLKSource=RCC_SYSCLKSOURCE_PLLCLK
board=custom

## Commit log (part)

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2024-03-23 Updated schematics
2024-03-23 Continue working on board layout
2024-03-24 Lay out more components
2024-03-24 Updated board layout
2024-03-25 Fix unconnected GND
2024-03-25 Misplaced one track on 20P connector
2024-04-21 Fixed ATX-24 pinout numbering
2024-04-21 Add power components
2024-04-21 Replace TI USB PD with ST USB PD
2024-04-24 Add TPS65987D charger circuit
2024-04-24 Replace AOSP21321 with AON7403 and update 3D models
2024-04-25 new power blocks
2024-04-25 Laid out components for power circuits
2024-04-26 Rewired PCIe without redriver
2024-04-26 Add CC values to DFP ports
2024-04-26 Renamed some connector pins
2024-04-27 Added MCU
2024-04-27 Fixed all DRC errors
2024-04-27 Replaced 12.4k resistor with two basic parts
2024-04-28 Increased inductor size
2024-05-01 Add initial MCU project
2024-05-04 Fixed USB Hub wrong net 1V0 -> 3V3
2024-05-05 Added initial FSM in MCU code
2024-05-11 Improvements to board
    * Break up power switch into input and output signals
    * Removed POWER_EN from USB PD charger (GPIO does not work due to one event per pin)
    * Added MOSFET to buffer GPIO output from PD IC
2024-05-15 Implemented MCU firmware
2024-05-18 Fixed power connector, PCIe direction, and MCU changes
2024-05-18 Add MCU schematics
2024-05-18 Update board version
2024-05-18 Added documentation
2024-05-18 Remove PCIe leech project
2024-07-01 Update firmware for rev 3 board
2024-07-03 Fix flipped MOSFETs for PDO signals
2024-07-03 Mislabeled I2C pin GND and 3V3
2024-07-05 Fix external board power toggle
2024-07-14 Replace TH PCI-E slot with SMD
2024-07-14 Add external board detect pin to MCU
2024-07-14 Fix missing GND connection & update name
2024-07-18 Implemented I2C communication
2024-07-18 Add external board detect to MCU
2024-07-18 Add debug config
2024-07-19 Added 3D model of new PCI-E slot
2024-07-21 Add XGMActivator project
2024-07-21 Fix I2C issue when 0xE6 is spammed
2024-07-21 Updated documentation
2024-07-21 Make sure photo credits show up
2024-07-21 Updated links to references
2024-07-21 Misnamed gitignore
2024-07-21 Updated diary
2024-07-21 Confirmed that only PCIe 3.0 works
2024-07-28 Increase thermal mass under 1V0 LDO
2024-07-28 Ensure SPI flash is powered on even when board loses power
2024-07-28 Move 1V0 LDO farther away from USB IC to reduce thermal load
2024-07-28 Bumped version to v0.4.1
2024-07-31 Replace AP7331-10WG-7 with AP7361-10ER-13 to handle power draw
2024-08-02 Increased heat sink area of 1V0 LDO
2024-08-04 Add TI PD project
2024-08-04 XGMActivator: fix typo
2024-08-06 Add power riser design
2024-08-06 MCU: move external board toggle to cable connect time
2024-08-06 docs: update diary with completed build
2024-08-07 pcb: added lite variant
2024-08-07 docs: updated build guide for lite builds
2024-08-08 pcb: redesign lite for the ADT-UT3G
2024-08-08 pcb: add 12V pad for external fan connection
2024-08-09 docs: updated diary to detail io shield
2024-08-09 docs: add lite image to readme
2024-08-23 pcb: use 0.3/0.4 vias for reduced cost on lite design
2024-08-31 pcb: redid layout for USB hub
2024-09-01 pcb: updated all via sizes to >= 0.4/0.3
2024-09-01 pcb: replaced 20P slot with mirrored connector
2024-09-01 mcu: updated GPIO pins for v0.5
2024-09-01 docs: update build guide
2024-09-01 pcb: improve thermal reliefs for pth
2024-09-01 pcb: move 20P crossover to cable
2024-09-24 pcb: add USB hub test board
2024-09-24 pcb: add project file for lite board
2024-09-24 pcb: add EPS12V adapter
2024-09-24 pcb: connect SPI flash to VIA IC
2024-09-24 diary: add cuda-z score
2024-10-22 xgmdriver: implement HID driver
2024-10-24 xgmdriver: add empty project to inhibit ASUS driver popup
2024-11-03 ti: updated charger project to use 65W and ASUS VID
2024-11-03 docs: updated diary and build guide for v5
2024-11-10 docs: document more commands using real XGM
2024-11-10 mcu: updated state machine to more closely match real XGM
2024-11-10 mcu: turn on red light when power is on
2024-11-10 driver: fix incorrect model in setup
2024-11-10 mcu: support standby mode
2024-12-10 pcb: add 12V PCIe power converters
2024-12-12 pcb: added fans and thermistor to standard pcb
2024-12-12 pcb: changed 1206 capacitors to 1210 since they are easier to source
2024-12-13 pcb: reduced gate resistor in schematic review
    Also updated some missing attributes.
2024-12-13 pcb: changed standard board to 6 layer because it is cheaper on JLCPCB
2024-12-25 pcb: reset size of alignment holes for PCIe slot
2025-01-10 pcb: fixed fan capacitor and changed case led resistor value
2025-01-10 mcu: add PWM fan control
    Also changed clock to 32MHz in order to handle PWM GPIO.
2025-01-11 pcb: disable hiccup mode on psu
2025-01-14 pcb: restore gnd connection to mounting screw
2025-01-16 mcu: start and stop the fans at the right time
2025-01-16 mcu: add missing files
2025-01-16 pcb: add pwm fans to lite board
2025-01-16 docs: updated documentation
2025-01-16 pcb: correct I2C labels on lite board
2025-01-17 pcb: fixed wrong voltage decoupling capacitor for PP_HV
2025-01-17 docs: updated lite board image
2025-02-01 mcu: add delay before asserting PWROK
2025-02-02 docs: updated for rev 6
2025-03-16 added more schematic and footsprint stuff
2025-03-16 added more schematic
2025-03-17 added more things to the schematic for proper wiring of open pins with high and low resistors
2025-03-17 more pcb changes
2025-03-17 almost finished everything
2025-03-17 fixed wrong 3.3v path
2025-03-17 routed 3v
2025-03-17 added thicker 3.3 track in middle layer
2025-03-17 slight correction to 3.3v trace
2025-03-17 added proper text on board
2025-03-17 better routing of the pcie clock trace
2025-03-18 final changes, still need to recheck
2025-03-18 more preparations for building the board
2025-03-18 minor tweak to the footprint of the redriver to keep the paste away from the sides
2025-03-18 more fixes and preparations for final assembly
2025-03-18 final changes before creating this
2025-03-18 more changes to support better pcb
2025-03-19 fixed part numbers
2025-03-19 fixed pcie 8 power connector part number
2025-03-19 added pcie model 8 model
2025-03-19 updated part number for molex with latest one
2025-03-20 updated flow version with proper design
2025-03-20 added part numbers to pcie power connector
2025-03-20 updated 12v clearances to make it safer
2025-03-20 better zone for 12v
2025-03-20 better clearnge 12v from pcie slot
2025-03-20 updated schematics and pcb
2025-03-20 updated pcb and forgot some clearance for 12v
2025-03-20 cleaned up track roung a bit
2025-04-07 more changes
2025-04-10 docs: add power board documentation
2025-04-10 docs: add related projects to readme
2025-05-04 power: added power board
2025-05-04 project: remove unused files
2026-01-15 pcb: add PWON# and power LED to lite board
2026-01-15 docs: update build guide for latest JLCPCB
2026-01-15 pcb: fix track width for co-planar waveguide
2026-01-16 pcb: fix +3.3V rail for cable LED
